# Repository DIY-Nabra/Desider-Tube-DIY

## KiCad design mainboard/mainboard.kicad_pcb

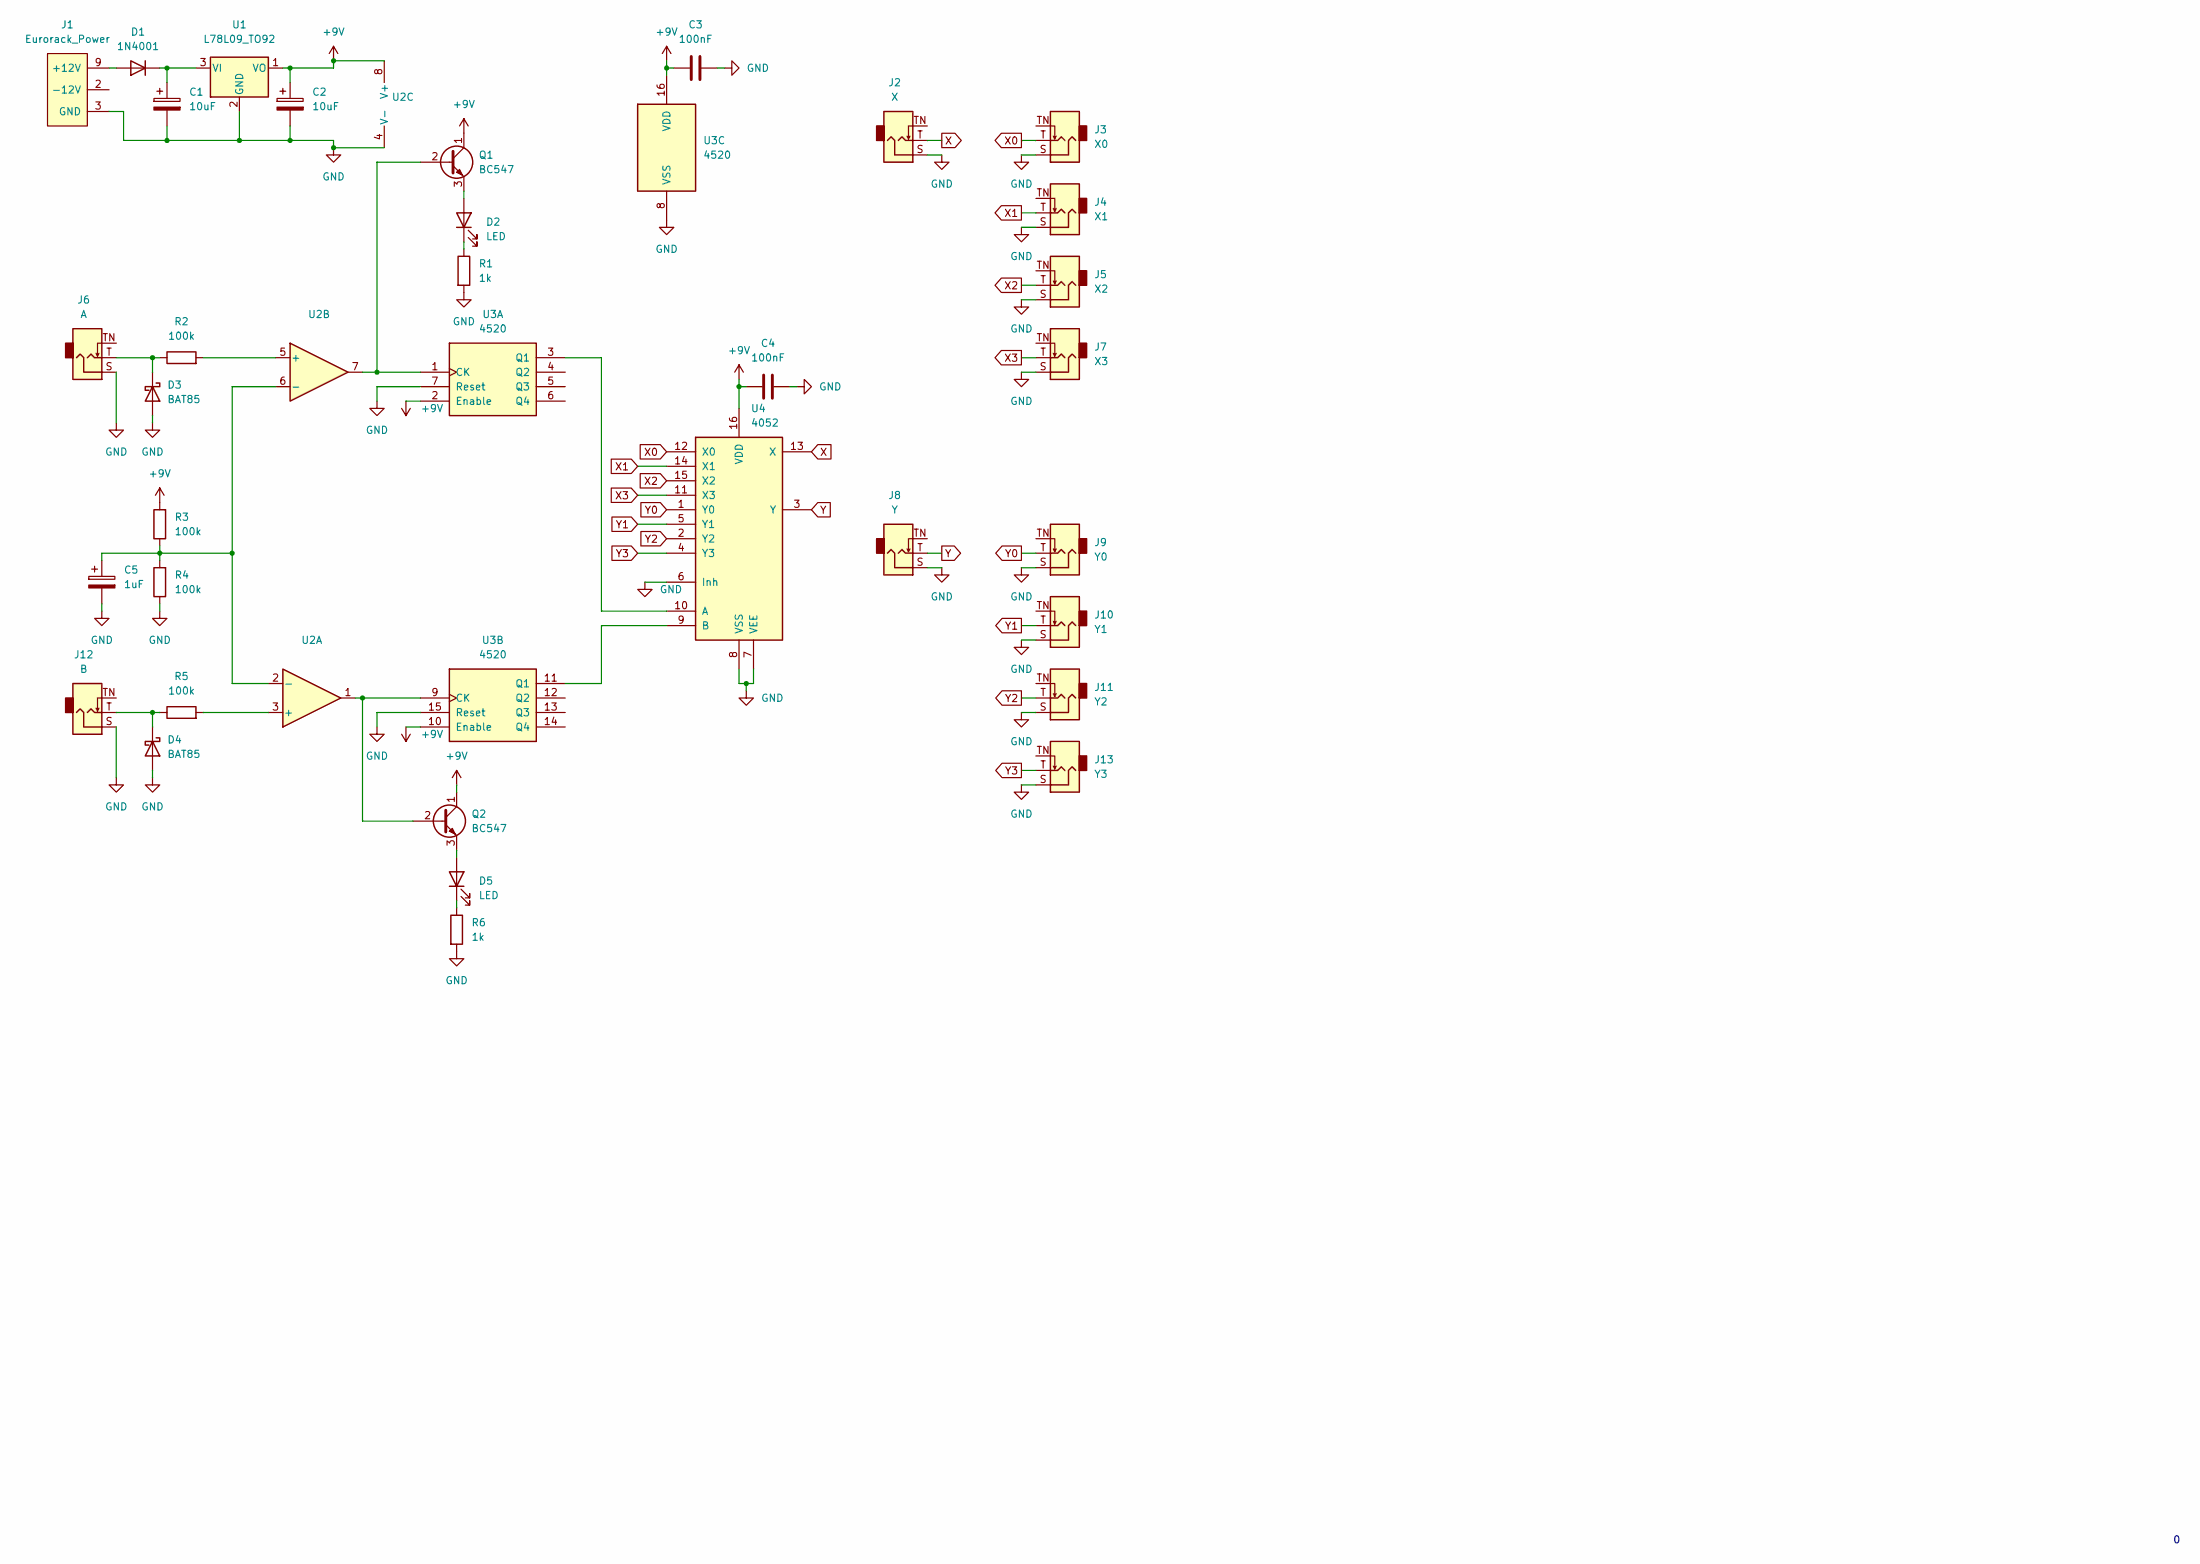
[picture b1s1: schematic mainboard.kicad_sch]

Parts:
C1, C2: 10uF; CP_Radial_D5.0mm_P2.50mm
C3, C4: 100nF; C_Disc_D3.8mm_W2.6mm_P2.50mm
C5: 1uF; CP_Radial_D5.0mm_P2.50mm
D1: 1N4001; D_DO-41_SOD81_P10.16mm_Horizontal
D2, D5: LED; LED_D3.0mm
D3, D4: BAT85; D_DO-35_SOD27_P7.62mm_Horizontal
J1: Eurorack_Power; Eurorack_Power_2x5_Shrouded; mpn 302-S101
J2: X; AudioJack_WQP518MA; MPN WQP-WQP518MA
J3: X0; AudioJack_WQP518MA; MPN WQP-WQP518MA
J4: X1; AudioJack_WQP518MA; MPN WQP-WQP518MA
J5: X2; AudioJack_WQP518MA; MPN WQP-WQP518MA
J6: A; AudioJack_WQP518MA; MPN WQP-WQP518MA
J7: X3; AudioJack_WQP518MA; MPN WQP-WQP518MA
J8: Y; AudioJack_WQP518MA; MPN WQP-WQP518MA
J9: Y0; AudioJack_WQP518MA; MPN WQP-WQP518MA
J10: Y1; AudioJack_WQP518MA; MPN WQP-WQP518MA
J11: Y2; AudioJack_WQP518MA; MPN WQP-WQP518MA
J12: B; AudioJack_WQP518MA; MPN WQP-WQP518MA
J13: Y3; AudioJack_WQP518MA; MPN WQP-WQP518MA
Q1, Q2: BC547; TO-92_Inline
R1, R6: 1k; R_Axial_DIN0204_L3.6mm_D1.6mm_P7.62mm_Horizontal
R2, R3, R4, R5: 100k; R_Axial_DIN0204_L3.6mm_D1.6mm_P7.62mm_Horizontal
U1: L78L09_TO92; TO-92_Inline
U2: (no value)
U3: 4520; DIP-16_W7.62mm_Socket
U4: 4052; DIP-16_W7.62mm_Socket

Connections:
+9V: C2.1, C3.1, C4.1, Q1.1 (C), Q2.1 (C), R3.2, U1.1 (VO), U2.8 (V+), U3.2 (Enable), U3.10 (Enable), U3.16 (VDD), U4.16 (VDD)
GND: C1.2, C2.2, C3.2, C4.2, C5.2, D3.2 (A), D4.2 (A), J1.3 (GND), J1.4 (GND), J1.5 (GND), J1.6 (GND), J1.7 (GND), J1.8 (GND), J2.S (Sleeve), J3.S (Sleeve), J4.S (Sleeve), J5.S (Sleeve), J6.S (Sleeve), J7.S (Sleeve), J8.S (Sleeve), J9.S (Sleeve), J10.S (Sleeve), J11.S (Sleeve), J12.S (Sleeve), J13.S (Sleeve), R1.2, R4.1, R6.2, U1.2 (GND), U2.4 (V-), U3.7 (Reset), U3.8 (VSS), U3.15 (Reset), U4.6 (Inh), U4.7 (VEE), U4.8 (VSS)
unnamed: C1.1, D1.1 (K), U1.3 (VI)
unnamed: C5.1, R3.1, R4.2, U2.2 (-), U2.6 (-)
unnamed: D1.2 (A), J1.9 (+12V), J1.10 (+12V)
unnamed: D2.1 (K), R1.1
unnamed: D2.2 (A), Q1.3 (E)
unnamed: D3.1 (K), J6.T (Tip), R2.1
unnamed: D4.1 (K), J12.T (Tip), R5.1
unnamed: D5.1 (K), R6.1
unnamed: D5.2 (A), Q2.3 (E)
unnamed: J1.1 (-12V), J1.2 (-12V)
unnamed: Q1.2 (B), U2.7, U3.1 (CK)
unnamed: Q2.2 (B), U2.1, U3.9 (CK)
unnamed: R2.2, U2.5 (+)
unnamed: R5.2, U2.3 (+)
unnamed: U3.3 (Q1), U4.10 (A)
unnamed: U3.11 (Q1), U4.9 (B)
X: J2.T (Tip), U4.13 (X)
X0: J3.T (Tip), U4.12 (X0)
X1: J4.T (Tip), U4.14 (X1)
X2: J5.T (Tip), U4.15 (X2)
X3: J7.T (Tip), U4.11 (X3)
Y: J8.T (Tip), U4.3 (Y)
Y0: J9.T (Tip), U4.1 (Y0)
Y1: J10.T (Tip), U4.5 (Y1)
Y2: J11.T (Tip), U4.2 (Y2)
Y3: J13.T (Tip), U4.4 (Y3)

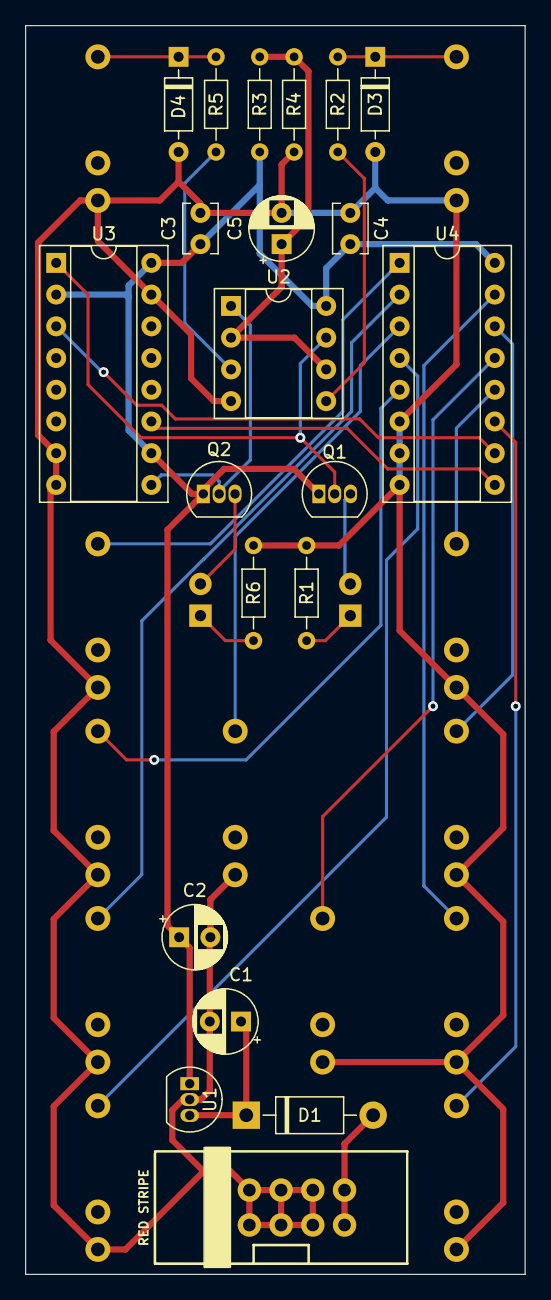
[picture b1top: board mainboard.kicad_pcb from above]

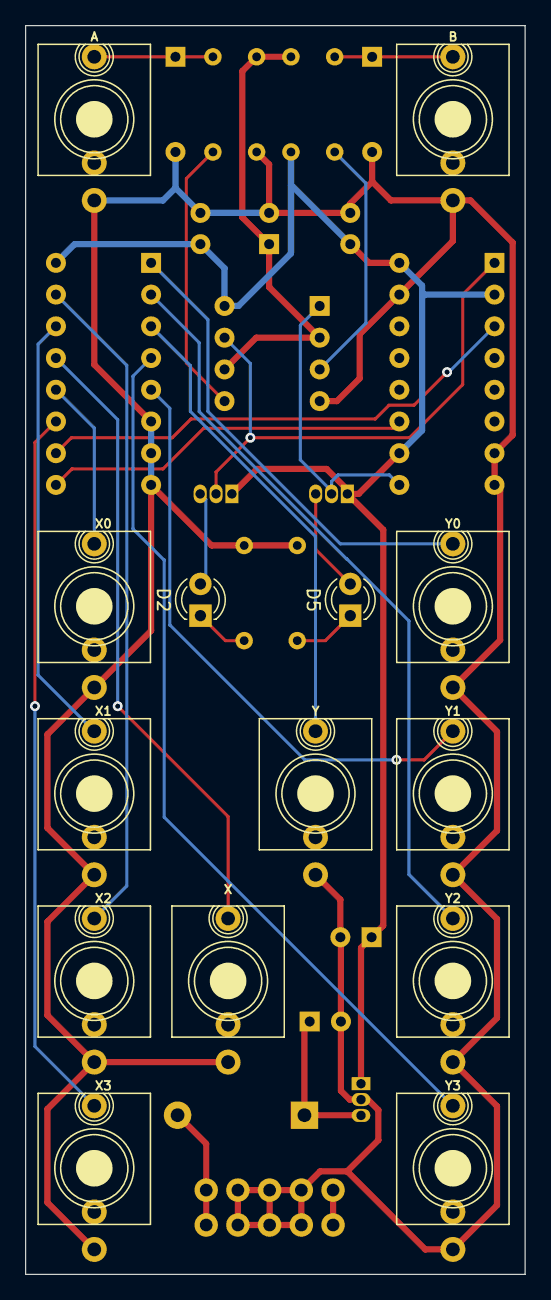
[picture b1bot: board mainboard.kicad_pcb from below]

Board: 2 copper layers, 40.0 x 100.0 mm, 35 parts (14 on the bottom side), 28 nets.
